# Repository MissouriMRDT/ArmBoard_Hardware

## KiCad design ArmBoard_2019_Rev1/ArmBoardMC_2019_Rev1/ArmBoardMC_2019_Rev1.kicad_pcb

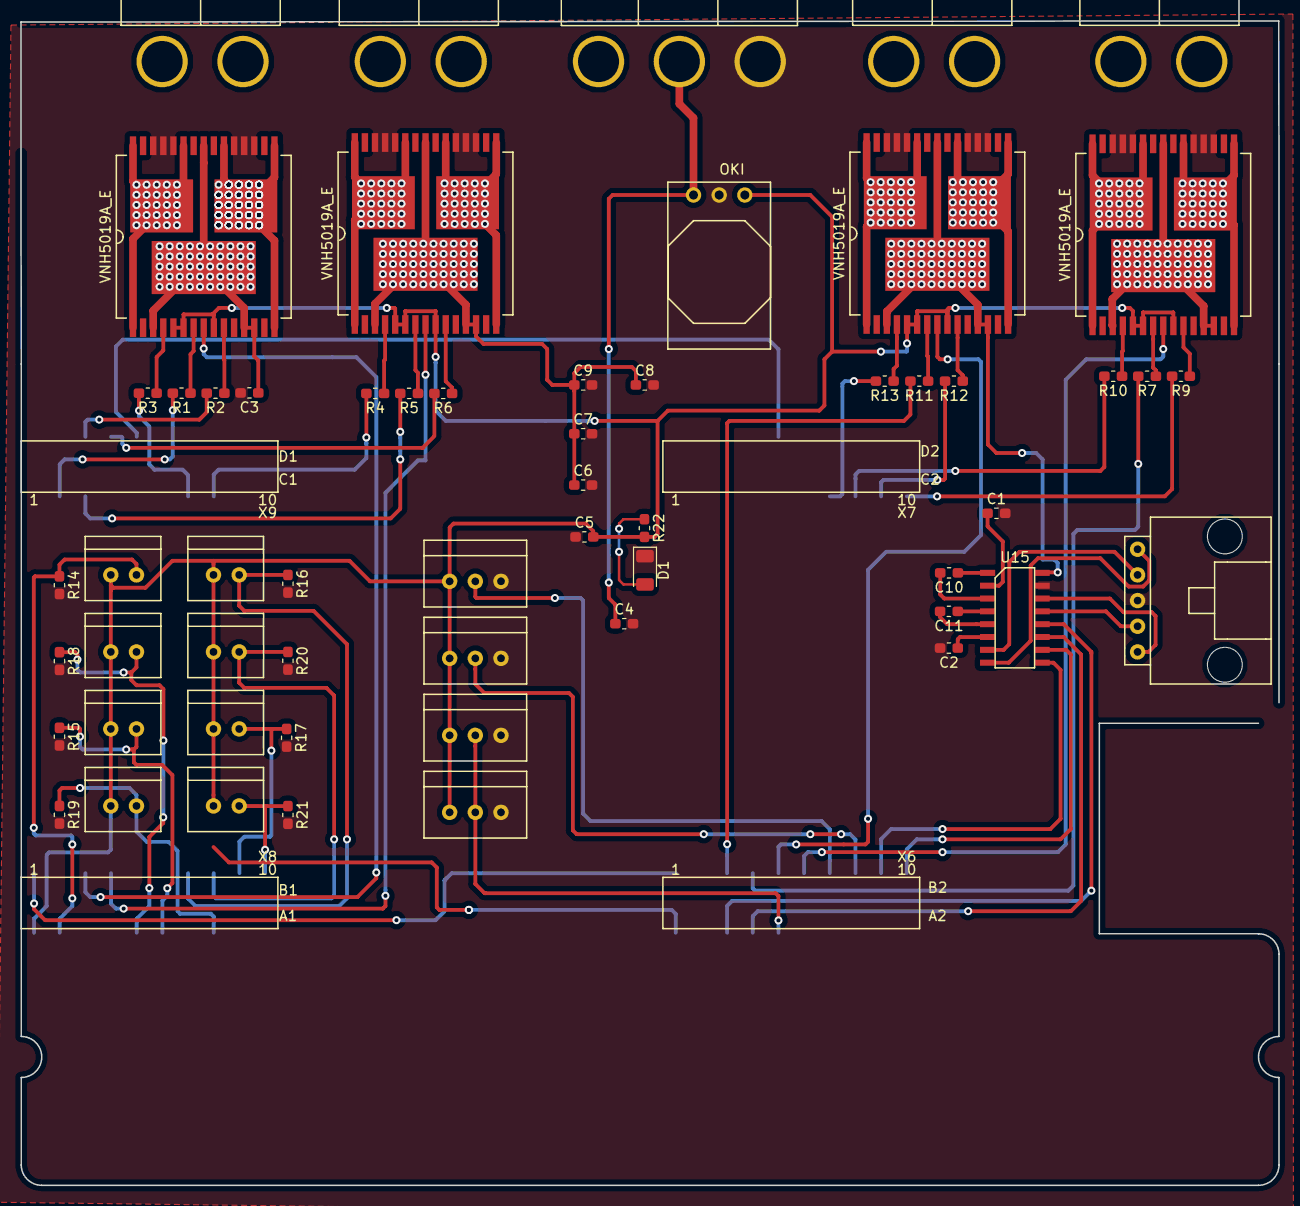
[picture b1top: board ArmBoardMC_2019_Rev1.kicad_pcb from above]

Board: 2 copper layers, 124.5 x 115.2 mm, 58 parts (0 on the bottom side), 66 nets.

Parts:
C1, C2, C10, C11: .1uF; C_0603_1608Metric_Pad1.05x0.95mm_HandSolder
C3: .1u; C_0603_1608Metric_Pad1.05x0.95mm_HandSolder
C4, C5, C6, C7, C8, C9: 10u; C_0603_1608Metric_Pad1.05x0.95mm_HandSolder
Conn1, Conn2, Conn3, Conn4: AndersonPP; Anderson_2_Horisontal_Side_by_Side
Conn5: Molex_SL_05; MOLEX_SL_05_Horizontal
Conn6: Anderson-3; Anderson_3_Horisontal_Side_by_Side
D1: LED; D_1206_3216Metric
R1, R2, R3, R4, R5, R6, R7, R9, R10, R11, R12, R13: 1K; R_0603_1608Metric_Pad1.05x0.95mm_HandSolder
R14, R15, R16, R17, R18, R19, R20, R21: 10K; R_0603_1608Metric_Pad1.05x0.95mm_HandSolder
R22: 330; R_0603_1608Metric_Pad1.05x0.95mm_HandSolder
U1, U2, U5, U6: VNH5019A_E; MultiPowerSO_30
U3: TM4C129E_Launchpad; TM4C129E_Launchpad_FULL_Bottom_SMD
U7: Limit_Switch1; MOLEX_SL_02_Vertical
U8: Limit_Switch3; MOLEX_SL_02_Vertical
U9: Limit_Switch5; MOLEX_SL_02_Vertical
U10: Limit_Switch7; MOLEX_SL_02_Vertical
U11: Limit_Switch2; MOLEX_SL_02_Vertical
U12: Limit_Switch4; MOLEX_SL_02_Vertical
U13: Limit_Switch6; MOLEX_SL_02_Vertical
U14: Limit_Switch8; MOLEX_SL_02_Vertical
U15: MAX_3232; SOIC_16_3.9x9.9mm_Pitch1.27mm
U16: OKI; OKI_Horizontal
U17: Encoder_1; MOLEX_SL_03_Vertical
U18: Encoder_3; MOLEX_SL_03_Vertical
U19: Encoder_2; MOLEX_SL_03_Vertical
U20: Encoder_4; MOLEX_SL_03_Vertical

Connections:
+3V3: C5.2, R22.2, U1.5, U1.6, U1.9, U2.5, U2.6, U2.9, U5.5, U5.6, U5.9, U6.5, U6.6, U6.9, U7.1, U8.1, U9.1, U10.1, U11.1, U12.1, U13.1, U14.1, U16.3, U17.1, U18.1, U19.1, U20.1
+12V: C3.1, C6.1, C7.1, C8.1, C9.1, Conn6.3, U1.3, U1.12, U1.13, U1.23, U1.32, U2.3, U2.12, U2.13, U2.23, U2.32, U5.3, U5.12, U5.13, U5.23, U5.32, U6.3, U6.12, U6.13, U6.23, U6.32, U15.16
/Out_A1: Conn1.1, U1.1, U1.25, U1.30, U1.31
/Out_A2: Conn2.1, U2.1, U2.25, U2.30, U2.31
/Out_A3: Conn3.1, U6.1, U6.25, U6.30, U6.31
/Out_A4: Conn4.1, U5.1, U5.25, U5.30, U5.31
/Out_B1: Conn1.2, U1.15, U1.16, U1.21, U1.33
/Out_B2: Conn2.2, U2.15, U2.16, U2.21, U2.33
/Out_B3: Conn3.2, U6.15, U6.16, U6.21, U6.33
/Out_B4: Conn4.2, U5.15, U5.16, U5.21, U5.33
/V+Log: C4.1, Conn6.2, U16.1
Encoder1_PWM: U3.PK2, U17.2
Encoder2_PWM: U3.PK3, U19.2
Encoder3_PWM: U3.PD4, U18.2, U20.2
GND: C1.2, C2.2, C3.2, C4.2, C5.1, C6.2, C7.2, C8.2, C9.2, Conn5.3, Conn6.1, D1.1, R14.2, R15.2, R16.2, R17.2, R18.2, R19.2, R20.2, R21.2, U1.18, U1.19, U1.20, U1.26, U1.27, U1.28, U2.18, U2.19, U2.20, U2.26, U2.27, U2.28, U3.GND, U5.18, U5.19, U5.20, U5.26, U5.27, U5.28, U6.18, U6.19, U6.20, U6.26, U6.27, U6.28, U15.15, U16.2, U17.3, U18.3, U19.3, U20.3
IN_A1: R3.2, U3.PL0
IN_A2: R4.2, U3.PL1
IN_A3: R13.2, U3.PH0
IN_A4: R10.2, U3.PH1
IN_B1: R2.2, U3.PH2
IN_B2: R6.2, U3.PH3
IN_B3: R12.2, U3.PK6
IN_B4: R9.2, U3.PK7
I_Sense_1: U1.8, U3.PE0
I_Sense_2: U2.8, U3.PE1
I_Sense_3: U3.PK0, U6.8
I_Sense_4: U3.PK1, U5.8
LS_1: R14.1, U3.PE4, U7.2
LS_2: R18.1, U3.PC6, U11.2
LS_3: R15.1, U3.PE5, U8.2
LS_4: R19.1, U3.PC7, U12.2
LS_5: R16.1, U3.PD7, U9.2
LS_6: R20.1, U3.PA6, U13.2
LS_7: R17.1, U3.PM4, U10.2
LS_8: R21.1, U3.PM5, U14.2
MOTOR1_PWM: R1.2, U3.PF2
MOTOR2_PWM: R5.2, U3.PF3
MOTOR3_PWM: R11.2, U3.PB4
MOTOR4_PWM: R7.2, U3.PB5
unnamed: C1.1, U15.2
unnamed: C2.1, U15.6
unnamed: C10.1, U15.1
unnamed: C10.2, U15.3
unnamed: C11.1, U15.4
unnamed: C11.2, U15.5
unnamed: D1.2, R22.1
unnamed: R1.1, U1.7
unnamed: R2.1, U1.10
unnamed: R3.1, U1.4
unnamed: R4.1, U2.4
unnamed: R5.1, U2.7
unnamed: R6.1, U2.10
unnamed: R7.1, U5.7
unnamed: R9.1, U5.10
unnamed: R10.1, U5.4
unnamed: R11.1, U6.7
unnamed: R12.1, U6.10
unnamed: R13.1, U6.4
RX_1_SL: Conn5.4, U15.13
RX_1_Tiva: U3.PP0, U15.12
RX_2_SL: Conn5.1, U15.8
RX_2_Tiva: U3.PA4, U15.9
TX_1_SL: Conn5.5, U15.14
TX_1_Tiva: U3.PP1, U15.11
TX_2_SL: Conn5.2, U15.7
TX_2_Tiva: U3.PA5, U15.10

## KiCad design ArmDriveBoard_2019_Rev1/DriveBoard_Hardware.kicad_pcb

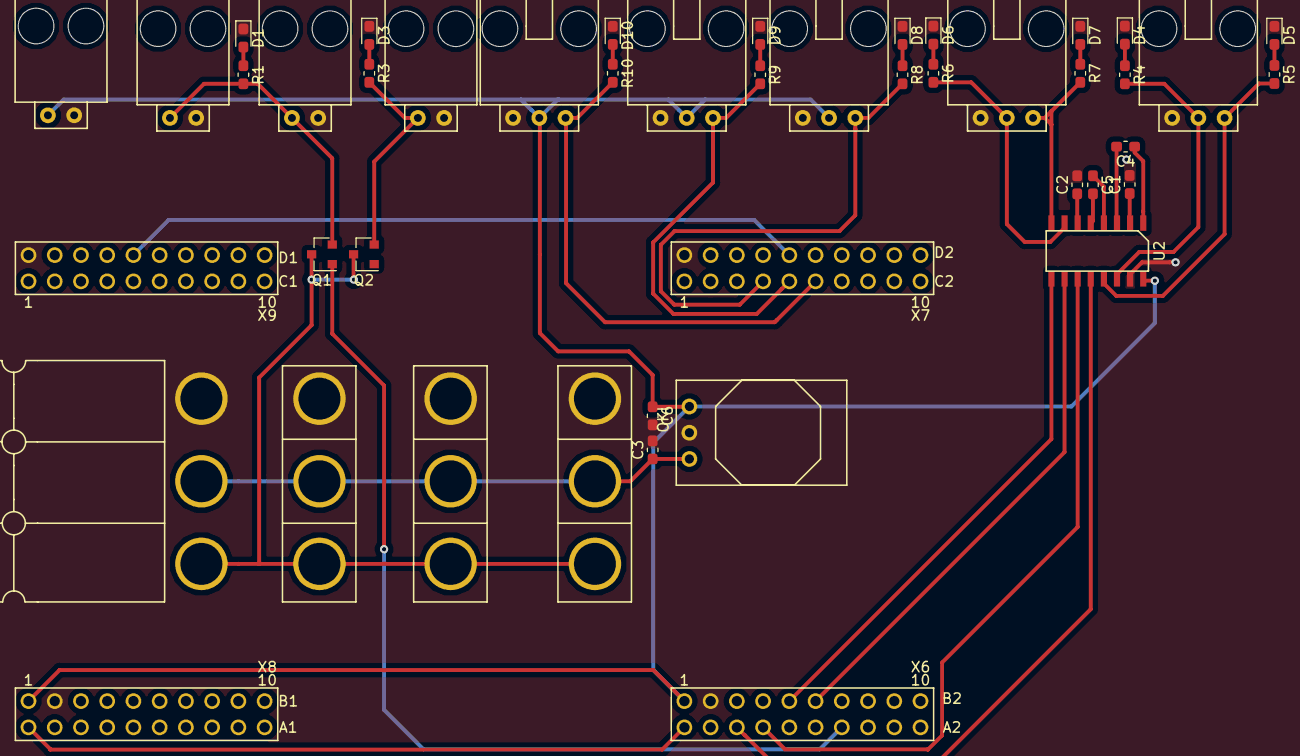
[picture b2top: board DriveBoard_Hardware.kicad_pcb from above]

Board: 2 copper layers, 42 parts (0 on the bottom side), 33 nets.

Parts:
C1, C2, C4, C5: .1uF; C_0603_1608Metric_Pad1.05x0.95mm_HandSolder
C3, C6: 10uF; C_0603_1608Metric_Pad1.05x0.95mm_HandSolder
Conn1, Conn10, Conn11, Conn12: AndersonPP; Anderson_3_Horisontal_Side_by_Side
Conn2: MoCo 1; MOLEX_SL_03_Horizontal
Conn3: MoCo 2; MOLEX_SL_03_Horizontal
Conn4: Laser 1; MOLEX_SL_02_Horizontal
Conn5: Laser 2; MOLEX_SL_02_Horizontal
Conn6: Solenoid; MOLEX_SL_02_Horizontal
Conn7: Servo 1; MOLEX_SL_03_Horizontal
Conn8: Servo 2; MOLEX_SL_03_Horizontal
Conn9: Servo 3; MOLEX_SL_03_Horizontal
Conn13: PowerOut; MOLEX_SL_02_Horizontal
D1, D3, D4, D5, D6, D7, D8, D9, D10: LED; LED_0603_1608Metric_Pad1.05x0.95mm_HandSolder
Q1, Q2: Q_NMOS_DGS; SOT-23
R1, R3: 1.5k; R_0603_1608Metric_Pad1.05x0.95mm_HandSolder
R4, R5, R6, R7, R8, R9, R10: 500; R_0603_1608Metric_Pad1.05x0.95mm_HandSolder
U1: TM4C129E_Launchpad; TM4C129E_Launchpad_FULL_ext
U2: MAX_3232; SOIC_16_3.9x9.9mm_Pitch1.27mm
U3: OKI; OKI_Horizontal

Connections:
+5V: C6.1, Conn7.2, Conn8.2, Conn9.2, Conn13.1, U1.+5V, U2.16, U3.3
+12V_Act: Conn1.3, Conn10.3, Conn11.3, Conn12.3, Q1.3, Q2.3
/+12V_log: C3.1, Conn1.2, Conn10.2, Conn11.2, Conn12.2, U3.1
GND: C1.2, C2.2, C3.2, C6.2, Conn1.1, Conn2.1, Conn3.1, Conn4.2, Conn5.2, Conn6.2, Conn7.1, Conn8.1, Conn9.1, Conn10.1, Conn11.1, Conn12.1, Conn13.2, D1.1, D3.1, D4.1, D5.1, D6.1, D7.1, D8.1, D9.1, D10.1, U1.GND, U2.15, U3.2
Laser_control: Q1.1, U1.PQ0
unnamed: C1.1, U2.2
unnamed: C2.1, U2.6
unnamed: C4.1, U2.1
unnamed: C4.2, U2.3
unnamed: C5.1, U2.4
unnamed: C5.2, U2.5
unnamed: Conn4.1, Conn5.1, Q1.2, R1.2
unnamed: Conn6.1, Q2.2, R3.2
unnamed: D1.2, R1.1
unnamed: D3.2, R3.1
unnamed: D4.2, R4.1
unnamed: D5.2, R5.1
unnamed: D6.2, R6.1
unnamed: D7.2, R7.1
unnamed: D8.2, R8.1
unnamed: D9.2, R9.1
unnamed: D10.2, R10.1
RX_1_IC: U1.PP0, U2.12
RX_1_SL: Conn2.3, R5.2, U2.13
RX_2_IC: U1.PK0, U2.9
RX_2_SL: Conn3.3, R7.2, U2.8
Servo1_PWM: Conn7.3, R8.2, U1.PM0
Servo2_PWM: Conn8.3, R9.2, U1.PM1
Servo3_PWM: Conn9.3, R10.2, U1.PM2
TX_1_IC: U1.PP1, U2.11
TX_1_SL: Conn2.2, R4.2, U2.14
TX_2_IC: U1.PK1, U2.10
TX_2_SL: Conn3.2, R6.2, U2.7

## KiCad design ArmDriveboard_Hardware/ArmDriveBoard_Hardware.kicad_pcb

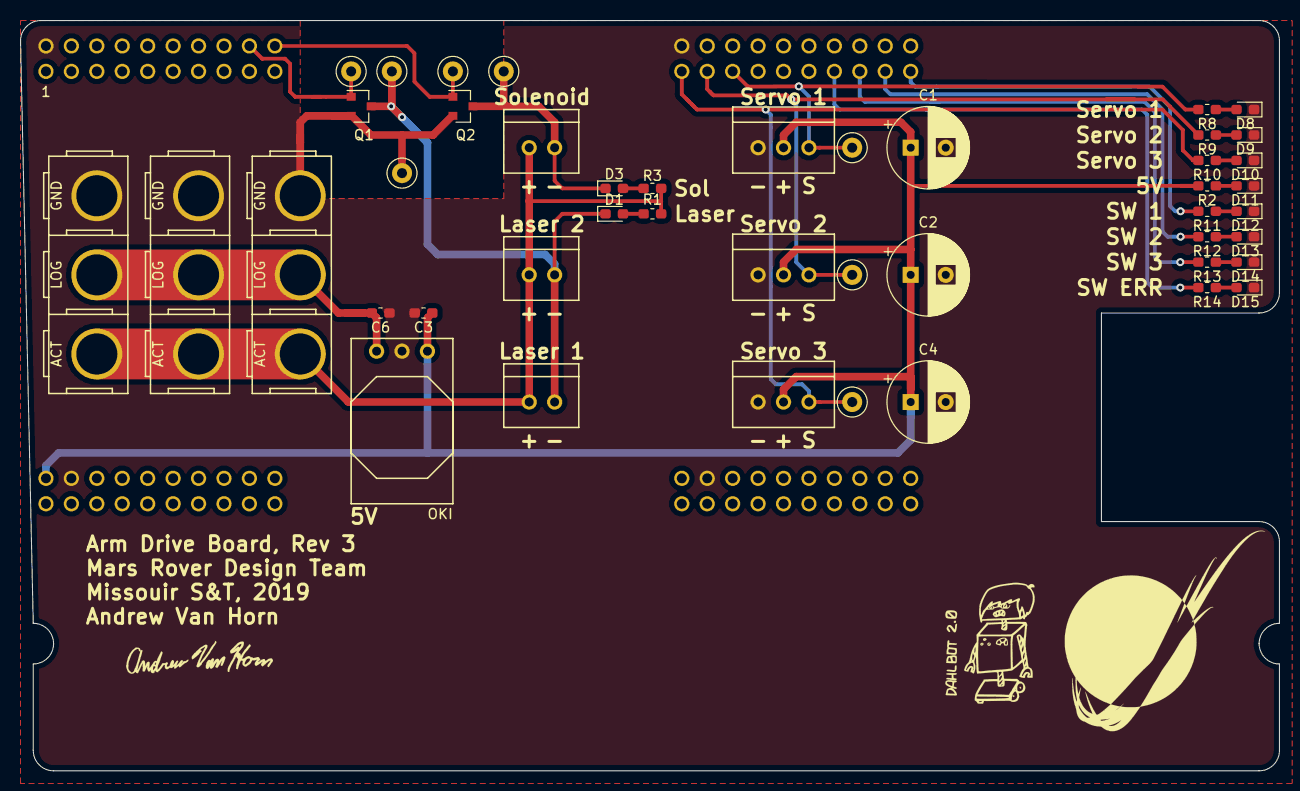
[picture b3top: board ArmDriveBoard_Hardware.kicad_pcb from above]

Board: 2 copper layers, 125.7 x 74.9 mm, 38 parts (0 on the bottom side), 25 nets.

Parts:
C1, C2, C4: CP; CP_Radial_D8.0mm_P3.50mm
C3, C6: 10uF; C_0603_1608Metric_Pad1.05x0.95mm_HandSolder
Conn4: Laser 1; MOLEX_SL_02_Vertical
Conn5: Laser 2; MOLEX_SL_02_Vertical
Conn6: Solenoid; MOLEX_SL_02_Vertical
Conn7: Servo 1; MOLEX_SL_03_Vertical
Conn8: Servo 2; MOLEX_SL_03_Vertical
Conn9: Servo 3; MOLEX_SL_03_Vertical
Conn10, Conn11, Conn12: AndersonPP; Anderson_3_Vertical_Side_by_Side
D1, D3: OrangeLED; LED_0603_1608Metric_Pad1.05x0.95mm_HandSolder
D8, D9, D10: YellowLED; LED_0603_1608Metric_Pad1.05x0.95mm_HandSolder
D11: GreenLED; LED_0603_1608Metric_Pad1.05x0.95mm_HandSolder
D12, D13, D14: BlueLED; LED_0603_1608Metric_Pad1.05x0.95mm_HandSolder
D15: RedLED; LED_0603_1608Metric_Pad1.05x0.95mm_HandSolder
Q1, Q2: Q_NMOS_GSD; SOT-23
R1, R3: 1.5k; R_0603_1608Metric_Pad1.05x0.95mm_HandSolder
R2, R8, R9, R10, R11, R12, R13, R14: 500; R_0603_1608Metric_Pad1.05x0.95mm_HandSolder
U1: TM4C129E_Launchpad; TM4C129E_Launchpad_FULL_THT_BOTTOM
U3: OKI; OKI_Horizontal

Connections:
+5V: C1.1, C2.1, C3.1, C4.1, Conn7.2, Conn8.2, Conn9.2, R2.2, U1.+5V, U3.3
+12V: Conn4.1, Conn5.1, Conn6.1, Conn10.3, Conn11.3, Conn12.3, R1.2, R3.1
/V+Log: C6.2, Conn10.2, Conn11.2, Conn12.2, U3.1
GND: C1.2, C2.2, C3.2, C4.2, C6.1, Conn7.1, Conn8.1, Conn9.1, Conn10.1, Conn11.1, Conn12.1, D8.1, D9.1, D10.1, D11.1, D12.1, D13.1, D14.1, D15.1, Q1.2, Q2.2, U1.GND, U3.2
Laser_Control: Q1.1, U1.PN3
unnamed: Conn4.2, Conn5.2, D1.1, Q1.3
unnamed: Conn6.2, D3.1, Q2.3
unnamed: D1.2, R1.1
unnamed: D3.2, R3.2
unnamed: D8.2, R8.1
unnamed: D9.2, R9.1
unnamed: D10.2, R10.1
unnamed: D11.2, R2.1
unnamed: D12.2, R11.1
unnamed: D13.2, R12.1
unnamed: D14.2, R13.1
unnamed: D15.2, R14.1
SW_IND_1: R11.2, U1.PK7
SW_IND_2: R12.2, U1.PK6
SW_IND_3: R13.2, U1.PH1
SW_IND_ERR: R14.2, U1.PH0
Servo1_PWM: Conn7.3, R8.2, U1.PK5
Servo2_PWM: Conn8.3, R9.2, U1.PK4
Servo3_PWM: Conn9.3, R10.2, U1.PG1
Solenoid_Control: Q2.1, U1.PP2

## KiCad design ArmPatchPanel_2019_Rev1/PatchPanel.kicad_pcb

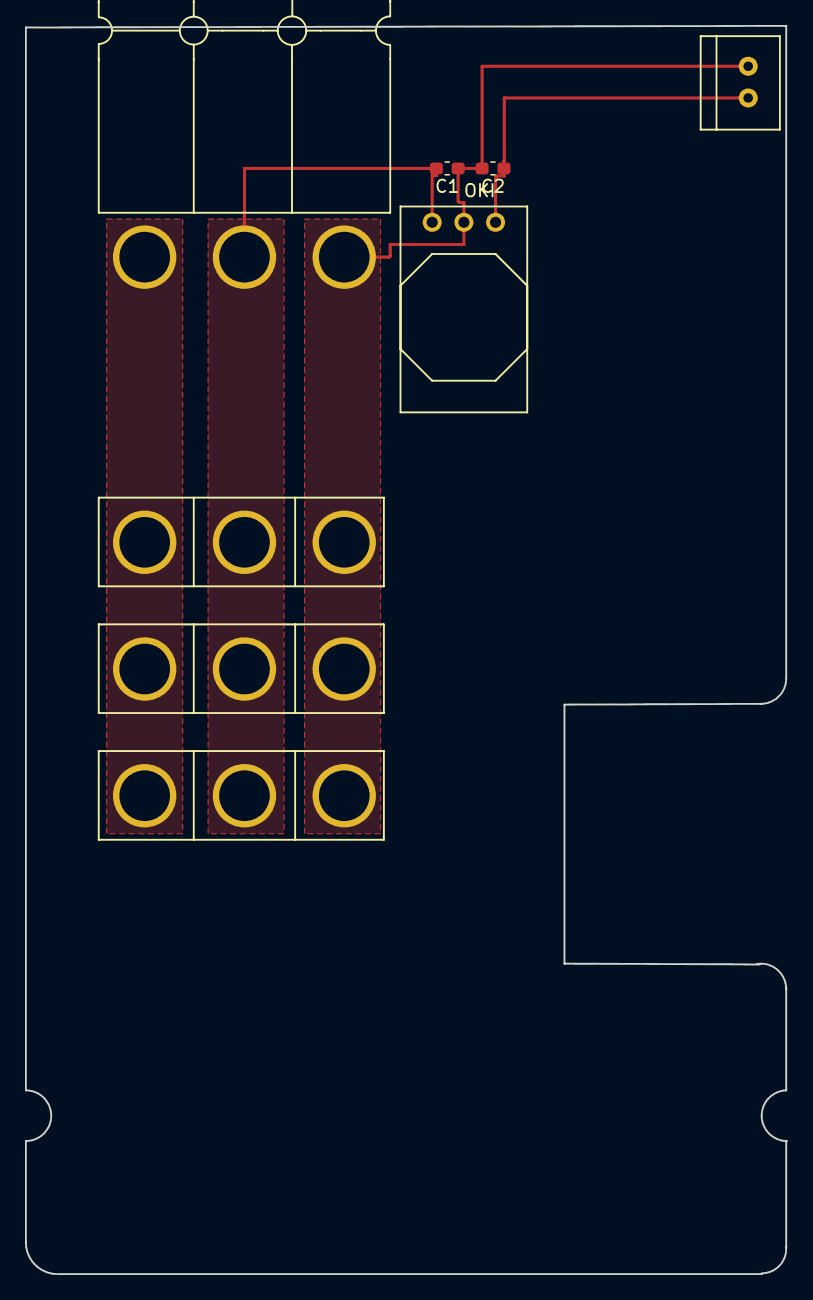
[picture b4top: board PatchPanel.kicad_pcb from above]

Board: 2 copper layers, 61.0 x 100.1 mm, 8 parts (0 on the bottom side), 4 nets.

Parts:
C1, C2: 10uF; C_0603_1608Metric_Pad1.05x0.95mm_HandSolder
Conn1, Conn2, Conn3, Conn4: AndersonPP; Anderson_3_Horisontal_Side_by_Side
Conn5: Molex_SL_02; MOLEX_SL_02_Vertical
U1: OKI; OKI_Horizontal

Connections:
/+5V: C2.1, Conn5.1, U1.3
/GND: C1.1, C2.2, Conn1.1, Conn2.1, Conn3.1, Conn4.1, Conn5.2, U1.2
unnamed: C1.2, Conn1.2, Conn2.2, Conn3.2, Conn4.2, U1.1
unnamed: Conn1.3, Conn2.3, Conn3.3, Conn4.3

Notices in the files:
parts and their libraries:
Copyright 2016 Accelerated Designs. All rights reserved.
